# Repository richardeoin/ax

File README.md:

## AX

This repository contains hardware and software for the AX5043 and
AX5243 radios from AxSemi (now ON Semiconductor). They are probably
the same die, but the AX5243 has fewer pins.

There is [hardware](hw/) for the Raspberry Pi, C.H.I.P. and a 2mm
pitch breakout board.

The [software](sw/) has both C and Python APIs, and can be used
without the cumbersome Ax-RadioLab GUI tool. Not all features of the
radio are supported yet.

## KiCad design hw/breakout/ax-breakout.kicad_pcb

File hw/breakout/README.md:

# Hardware for ax-breakout

This folder contains the schematic files for the ax-breakout header
board.

This board breaks out a single AX5243 radio to 2mm pitch pins. *Not yet tested*

The differential match can be populated for various frequencies, using
the values found in the AX5243 datasheet. Usually this is 144MHz,
434MHz or 868MHz. `Lext` can be populated so that frequencies outside
of 400-525MHz / 800-1050MHz can be used; usually this is `22nH` for
140-154MHz.

_[Schematics](ax-breakout.sch.pdf)_

_[Board Drawings](ax-breakout.kicad_pcb.pdf)_

_[3D Rendering](ax-breakout.kicad_pcb.png)_

![Rendering of ax-breakout board](ax-breakout.kicad_pcb.png
 "Rendering of ax-breakout board")

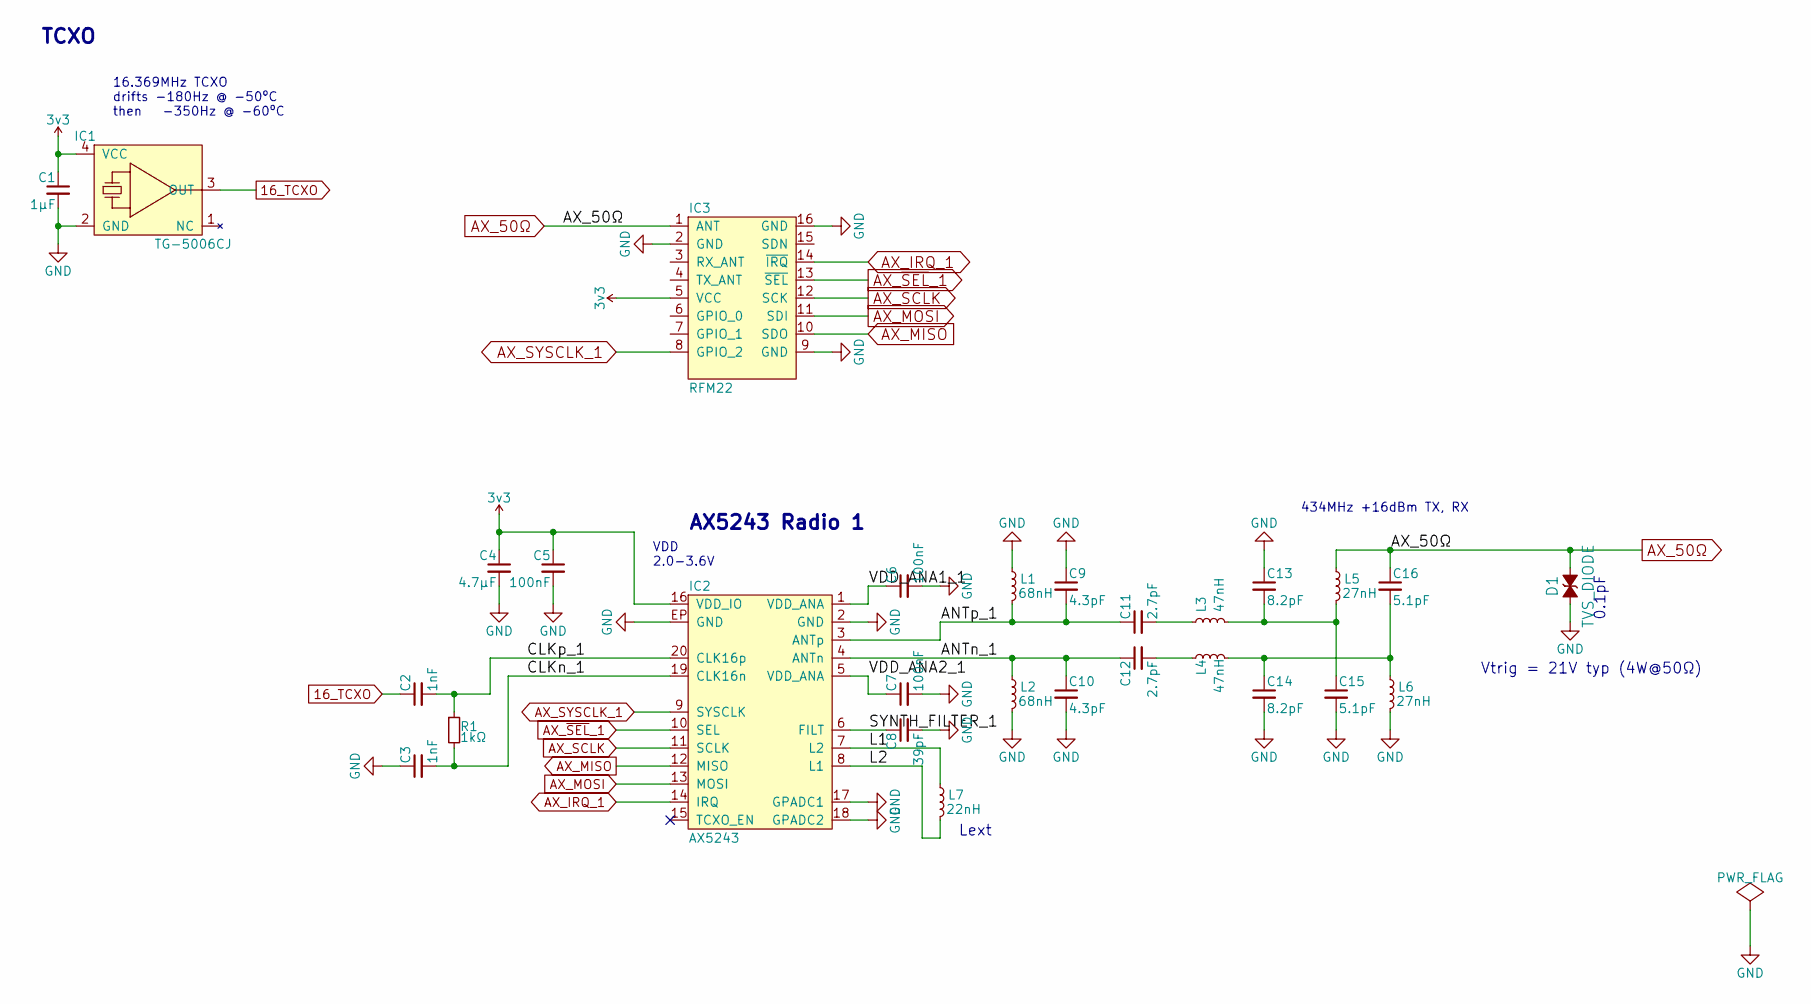
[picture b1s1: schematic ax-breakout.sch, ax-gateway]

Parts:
C1: 1µF; 0402
C2, C3: 1nF; 0402
C4: 4.7µF; 0402
C5, C6, C7: 100nF; 0402
C8: 39pF; 0402
C9, C10: 4.3pF; 0402
C11, C12: 2.7pF; 0402
C13, C14: 8.2pF; 0402
C15, C16: 5.1pF; 0402
D1: TVS_DIODE; TSLP-2-17; Farnell 2480929
IC1: TG-5006CJ; Farnell 2405790
IC2: AX5243; QFN-20-EP-AX; Farnell 2521322
IC3: RFM22; RFM22_COMPATIBLE
L1, L2: 68nH; 0402
L3, L4: 47nH; 0402
L5, L6: 27nH; 0402
L7: 22nH; 0402
R1: 1kΩ; 0402

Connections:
3v3: C1.1, C4.1, C5.1, IC1.4 (VCC), IC2.16 (VDD_IO), IC3.5 (VCC)
16_TCXO: C2.1, IC1.3 (OUT)
/ANTn_1: C10.1, C12.1, IC2.4 (ANTn), L2.1
/ANTp_1: C9.2, C11.1, IC2.3 (ANTp), L1.2
/CLKn_1: C3.2, IC2.19 (CLK16n), R1.2
/CLKp_1: C2.2, IC2.20 (CLK16p), R1.1
/L1: IC2.7 (L2), L7.1
/L2: IC2.8 (L1), L7.2
/SYNTH_FILTER_1: C8.1, IC2.6 (FILT)
/VDD_ANA1_1: C6.1, IC2.1 (VDD_ANA)
/VDD_ANA2_1: C7.1, IC2.5 (VDD_ANA)
AX_50Ω: C16.1, D1.1, IC3.1 (ANT), L5.1
AX_IRQ_1: IC2.14 (IRQ), IC3.14 (~IRQ~)
AX_MISO: IC2.12 (MISO), IC3.10 (SDO)
AX_MOSI: IC2.13 (MOSI), IC3.11 (SDI)
AX_SCLK: IC2.11 (SCLK), IC3.12 (SCK)
AX_SYSCLK_1: IC2.9 (SYSCLK), IC3.8 (GPIO_2)
AX_~SEL~_1: IC2.10 (SEL), IC3.13 (~SEL~)
GND: C1.2, C3.1, C4.2, C5.2, C6.2, C7.2, C8.2, C9.1, C10.2, C13.1, C14.2, C15.2, D1.2, IC1.2 (GND), IC2.2 (GND), IC2.17 (GPADC1), IC2.18 (GPADC2), IC2.EP (GND), IC3.2 (GND), IC3.9 (GND), IC3.16 (GND), L1.1, L2.2, L6.2
unnamed: C11.2, L3.1
unnamed: C12.2, L4.1
unnamed: C13.2, C15.1, L3.2, L5.2
unnamed: C14.1, C16.2, L4.2, L6.1

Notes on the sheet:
16.369MHz TCXO drifts -180Hz @ -50ºC then -350Hz @ -60ºC
AX5243 Radio 1
VDD 2.0-3.6V
TCXO
434MHz +16dBm TX, RX
Vtrig = 21V typ (4W@50Ω)
0.1pF
Lext

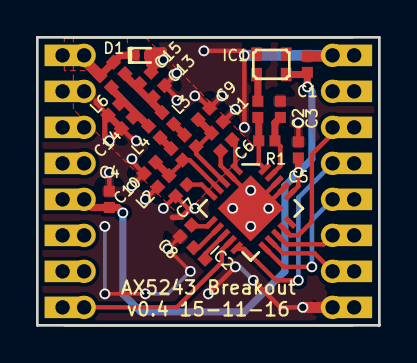
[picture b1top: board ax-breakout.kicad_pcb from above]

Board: 2 copper layers, 19.0 x 16.0 mm, 28 parts (0 on the bottom side), 23 nets.

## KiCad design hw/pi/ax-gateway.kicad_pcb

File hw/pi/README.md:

# Hardware for ax-gateway

This folder contains the schematic files for the ax-gateway header
board.

This board supports one or two AX5243 radios, with a bi-directional
antenna port for each radio. It has been tested with a
[Raspberry Pi 3 Model B](https://www.raspberrypi.org/products/raspberry-pi-3-model-b/).

The differential match can be populated for various frequencies, using
the values found in the AX5243 datasheet. Usually this is 144MHz,
434MHz or 868MHz. `Lext` can be populated so that frequencies outside
of 400-525MHz / 800-1050MHz can be used; usually this is `22nH` for
140-154MHz.

_[Schematics](ax-gateway.sch.pdf)_

_[Board Drawings](ax-gateway.kicad_pcb.pdf)_

_[3D Rendering](ax-gateway.kicad_pcb.png)_

![Assembled ax-gateway header board](ax-gateway-on-pi.jpg
 "Assembled ax-gateway header board")

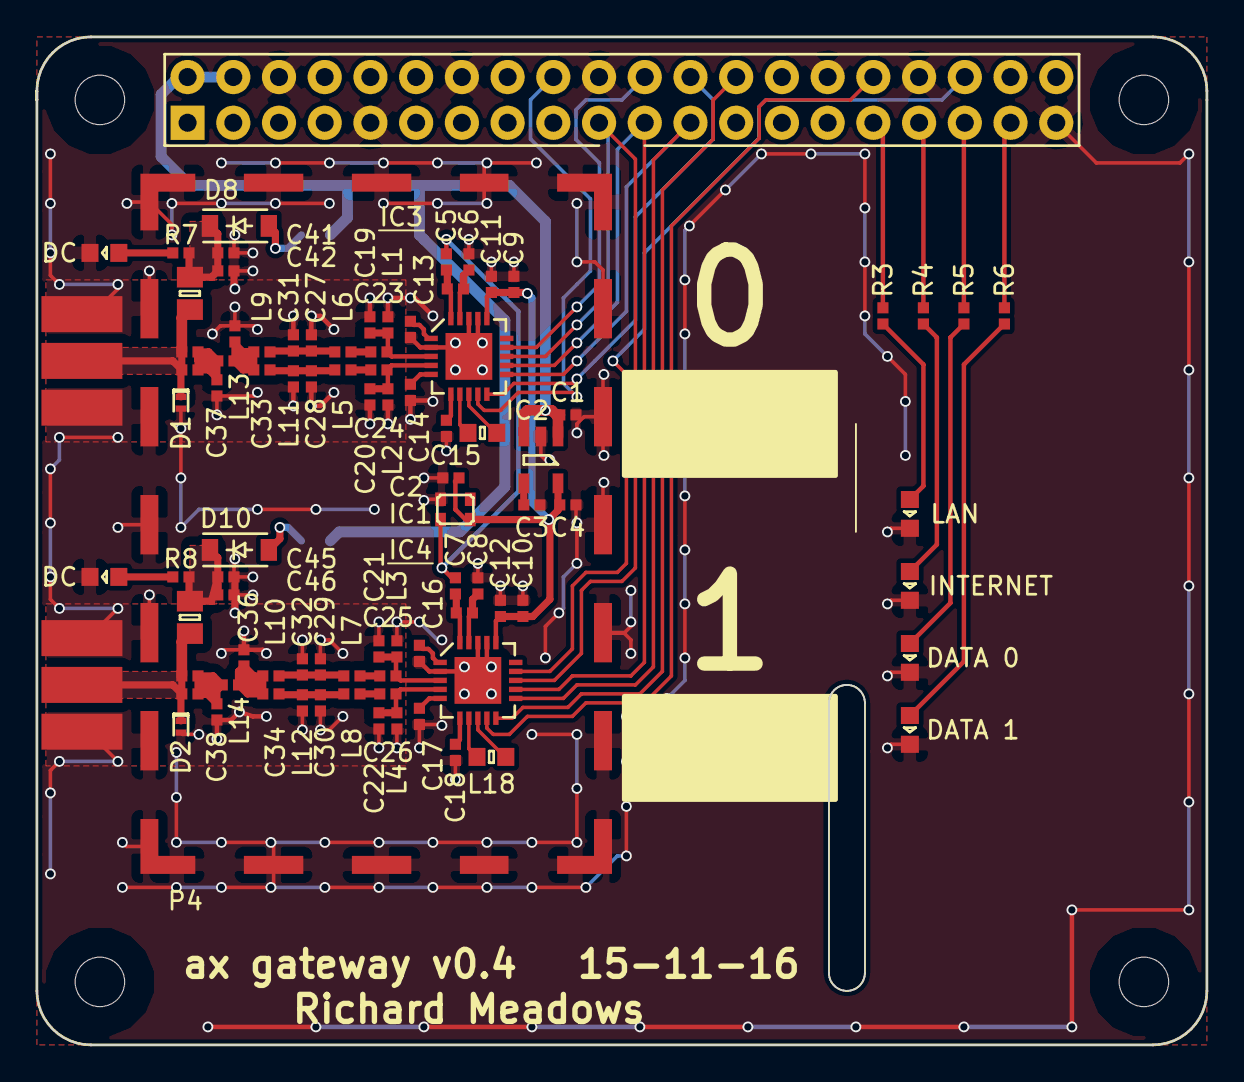
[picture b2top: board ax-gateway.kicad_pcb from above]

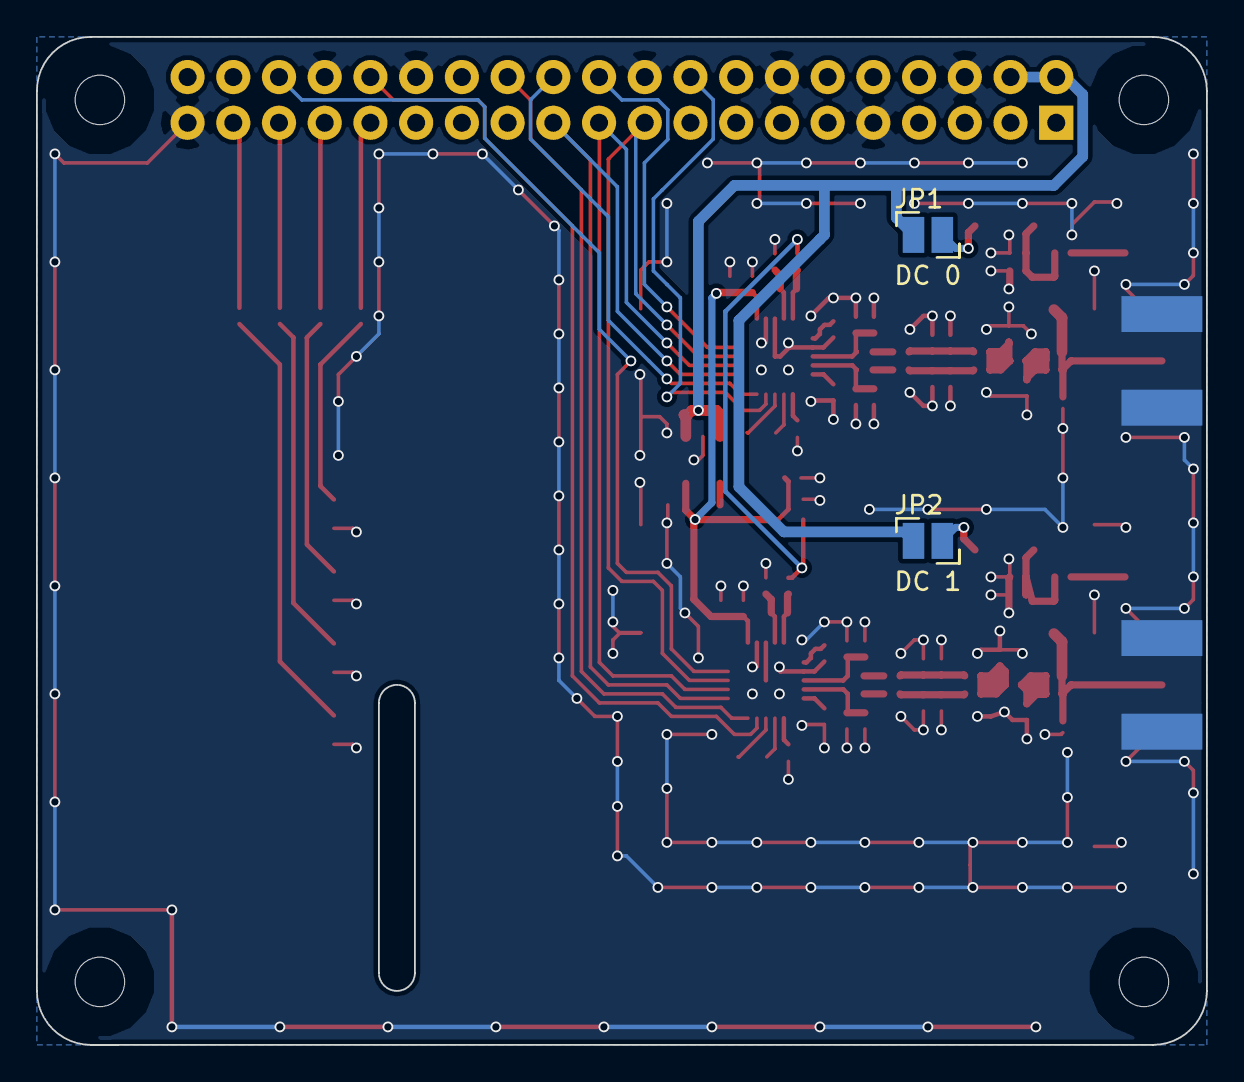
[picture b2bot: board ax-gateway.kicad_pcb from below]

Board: 2 copper layers, 65.0 x 56.0 mm, 92 parts (2 on the bottom side), 60 nets.

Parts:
C1, C2: 1µF; 0402
C3: 10nF; 0402
C4, C9, C10: 4.7µF; 0402
C5, C6, C7, C8, C39, C42, C43, C46: 1nF; 0402
C11, C12, C13, C14, C16, C17, C41, C45: 100nF; 0402
C15, C18: 39pF; 0402
C19, C20, C23, C24: 4.3pF; 0402
C21, C22: DNP; 0402
C25, C26, C32, C34: 2.7pF; 0402
C27, C28: 8.2pF; 0402
C29, C30: 3.6pF; 0402
C31, C33: 5.1pF; 0402
C35, C36, C37, C38: NOSTUFF; 0402
C40, C44: 100pF; 0402
D1, D2: TVS_DIODE; TSLP-2-17
D3: LAN; 0603-LED
D4: INTERNET; 0603-LED
D5: DATA 0; 0603-LED
D6: DATA 1; 0603-LED
D7: DC 1; 0603-LED
D8, D10: SCHOTTKY; SOD-123
D9: DC 0; 0603-LED
IC1: TG-5006CJ
IC2: TPS73433; SOT-23-5
IC3, IC4: AX5243; QFN-20-EP-AX
JP1, JP2: Jumper_NO_Small; SOLDER_JUMPER_NO
L1, L2: 68nH; 0402
L3, L4, L7, L8: 18nH; 0402
L5, L6: 47nH; 0402
L9, L11: 27nH; 0402
L10, L12: 12nH; 0402
L13, L14: 0Ω; 0402
L15, L16: 2.2µH; 0805
L17, L18: 22nH; 0603
P1: Raspberry_Pi_Conn; Rasberry_Pi_3
P2, P3: COAX; SMA-EDGE
P4: PAD; BMI-S-x05
R1, R2: 1kΩ; 0402
R3, R4, R5, R6, R7, R8: 330Ω; 0402

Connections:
3v3: C2.1, C4.1, C9.1, C10.1, C11.1, C12.1, IC1.4, IC2.5, IC3.16, IC4.16
16_TCXO: C5.1, C7.1, IC1.3
/ANTn_0: C20.1, C24.1, IC3.4, L2.1
/ANTn_1: C22.1, C26.1, IC4.4, L4.1
/ANTp_0: C19.2, C23.1, IC3.3, L1.2
/ANTp_1: C21.2, C25.1, IC4.3, L3.2
/AX_50Ω_0: C33.1, C35.1, L9.1, L13.1
/AX_50Ω_1: C34.1, C36.1, L10.1, L14.1
/AX_ANT_0: C39.2, C40.2, D1.1, L15.2, P2.1
/AX_ANT_1: C43.2, C44.2, D2.1, L16.2, P3.1
/AX_F_0: C37.1, C39.1, C40.1, L13.2
/AX_F_1: C38.1, C43.1, C44.1, L14.2
/CLKn_0: C6.2, IC3.19, R1.2
/CLKn_1: C8.2, IC4.19, R2.2
/CLKp_0: C5.2, IC3.20, R1.1
/CLKp_1: C7.2, IC4.20, R2.1
/DC_0: C41.1, C42.1, D8.1, L15.1, R7.1
/DC_1: C45.1, C46.1, D10.1, L16.1, R8.1
/L1_0: IC3.7, L17.1
/L1_1: IC4.7, L18.1
/L2_0: IC3.8, L17.2
/L2_1: IC4.8, L18.2
/SYNTH_FILTER_0: C15.1, IC3.6
/SYNTH_FILTER_1: C18.1, IC4.6
/VDD_ANA1_0: C13.1, IC3.1
/VDD_ANA1_1: C16.1, IC4.1
/VDD_ANA2_0: C14.1, IC3.5
/VDD_ANA2_1: C17.1, IC4.5
AX_IRQ_0: IC3.14, P1.22
AX_IRQ_1: IC4.14, P1.36
AX_MISO: IC3.12, IC4.12, P1.21
AX_MOSI: IC3.13, IC4.13, P1.19
AX_SCLK: IC3.11, IC4.11, P1.23
AX_SYSCLK_0: IC3.9, P1.18
AX_SYSCLK_1: IC4.9, P1.32
AX_~SEL~_0: IC3.10, P1.24
AX_~SEL~_1: IC4.10, P1.26
DATA_LED_0: P1.35, R5.1
DATA_LED_1: P1.37, R6.1
GND: C1.2, C2.2, C3.2, C4.2, C6.1, C8.1, C9.2, C10.2, C11.2, C12.2, C13.2, C14.2, C15.2, C16.2, C17.2, C18.2, C19.1, C20.2, C21.1, C22.2, C27.1, C28.2, C29.1, C30.2, C31.2, C32.2, C35.2, C36.2, C37.2, C38.2, C41.2, C42.2, C45.2, C46.2, D1.2, D2.2, D3.1, D4.1, D5.1, D6.1, D7.1, D9.1, IC1.2, IC2.2, IC3.2, IC3.17, IC3.18, IC3.EP, IC4.2, IC4.17, IC4.18, IC4.EP, L1.1, L2.2, L3.1, L4.2, L11.2, L12.2, P1.6, P1.9, P1.14, P1.20, P1.25, P1.30, P1.34, P1.39, P2.2, P3.2, P4.1
INTERNET_LED: P1.33, R4.1
LAN_LED: P1.31, R3.1
unnamed: C3.1, IC2.4
unnamed: C23.2, L5.1
unnamed: C24.2, L6.1
unnamed: C25.2, L7.1
unnamed: C26.2, L8.1
unnamed: C27.2, C31.1, L5.2, L9.2
unnamed: C28.1, C33.2, L6.2, L11.1
unnamed: C29.2, C32.1, L7.2, L10.2
unnamed: C30.1, C34.2, L8.2, L12.1
unnamed: D3.2, R3.2
unnamed: D4.2, R4.2
unnamed: D5.2, R5.2
unnamed: D6.2, R6.2
unnamed: D7.2, R8.2
unnamed: D8.2, JP1.2
unnamed: D9.2, R7.2
unnamed: D10.2, JP2.2
VDD: C1.1, IC2.1, IC2.3, JP1.1, JP2.1, P1.2, P1.4

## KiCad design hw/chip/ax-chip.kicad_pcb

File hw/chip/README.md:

# Hardware for ax-chip

This folder contains the schematic files for the ax-chip header
board.

The board uses a single AX5043 radio, with separate antenna ports for
transmit and receive. The recieve port has an integrated Low Noise
Amplifier (LNA). *Not yet tested*

The LNA used is an
[Avago MGA-62563](http://www.avagotech.com/docs/AV02-1237EN), but a
MGA-61563 or MGA-68563 could also be used, by adjusting the bias
resistor R12. By default the MGA-62563 is biased to 3.3V, 30mA.

| Frequency (MHz) | Theoretical NF @ 25ºC |
|---|---
| 144 | 1.3
| 434 | 0.9

The differential match following the LNA is tuned to for both 144MHz
and 434MHz (blue line in this [plot](144_434_S21.png)). The single
ended match on the transmit port is tuned for 144MHz, although other
values can be found in the AX5043 datasheet.

`Lext` can be populated so that frequencies outside of 400-525MHz /
800-1050MHz can be used; usually this is `22nH` for 140-154MHz.

_[Schematics](ax-chip.sch.pdf)_

_[Board Drawings](ax-chip.kicad_pcb.pdf)_

_[3D Rendering](ax-chip.kicad_pcb.png)_

<!-- ![Assembled ax-gateway header board](ax-gateway-on-pi.jpg -->
<!--  "Assembled ax-gateway header board") -->

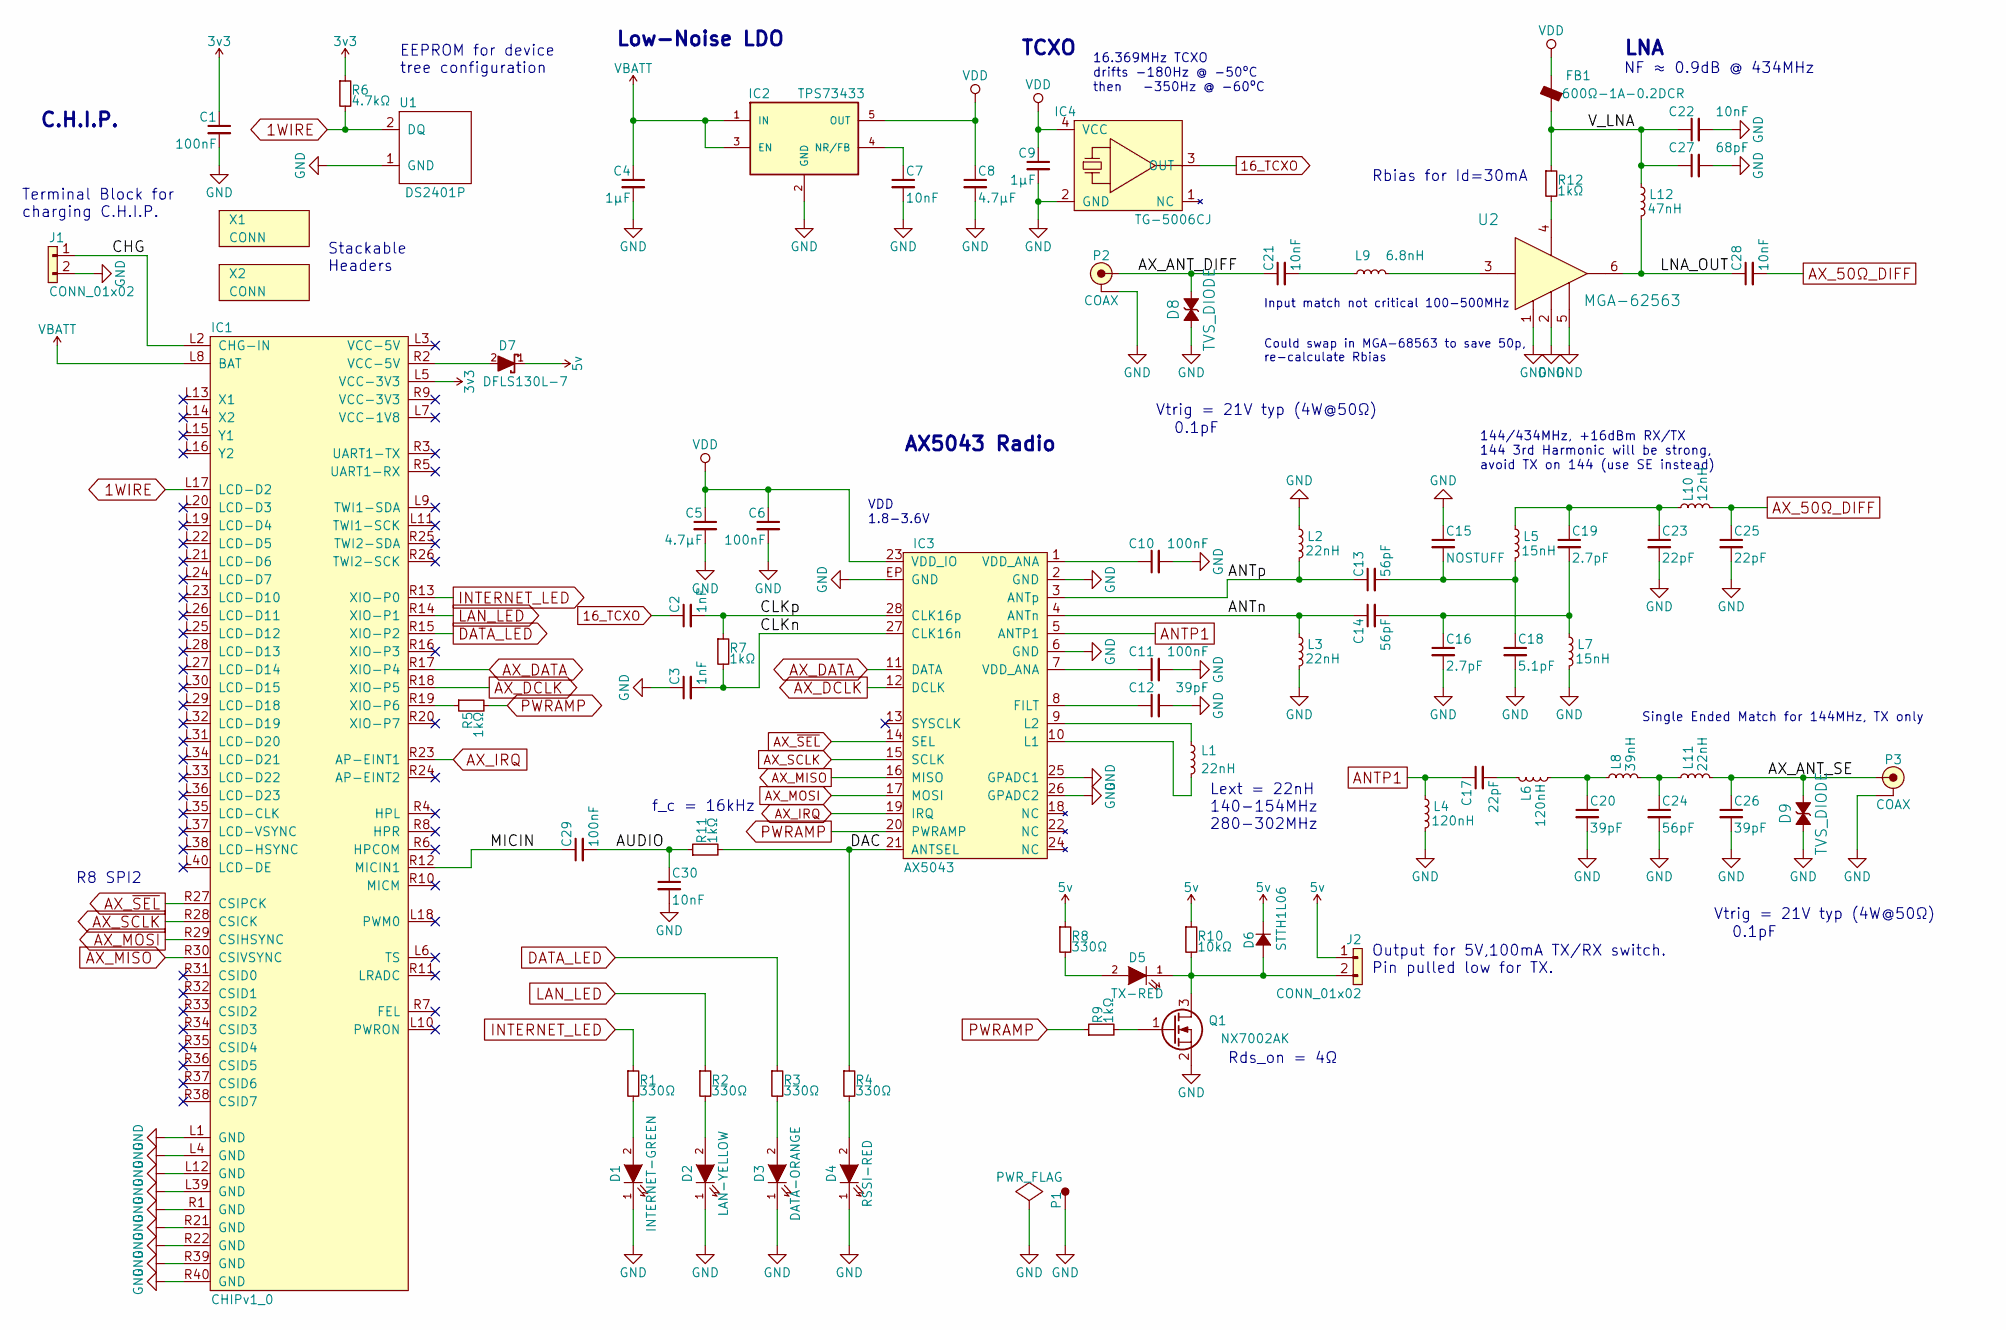
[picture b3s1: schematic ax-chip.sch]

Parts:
C1, C6, C10, C11, C29: 100nF; 0402
C2, C3: 1nF; 0402
C4, C9: 1µF; 0402
C5, C8: 4.7µF; 0402
C7, C22, C30: 10nF; 0402
C12, C20, C26: 39pF; 0402
C13, C14, C24: 56pF; 0402
C15: NOSTUFF; 0402
C16, C19: 2.7pF; 0402
C17, C23, C25: 22pF; 0402
C18: 5.1pF; 0402
C21, C28: 10nF; 0402; Farnell 8819734
C27: 68pF; 0402
D1: INTERNET-GREEN; 1206_LED_REVERSE; Farnell 2217901
D2: LAN-YELLOW; 1206_LED_REVERSE; Farnell 2217902
D3: DATA-ORANGE; 1206_LED_REVERSE; Farnell 2099254
D4: RSSI-RED; 1206_LED_REVERSE; Farnell 2217903
D5: TX-RED; 1206_LED_REVERSE; Farnell 2217903
D6: STTH1L06; DO-214AC-SMA; Farnell 8165505
D7: DFLS130L-7; SOD-123; Farnell 1843673
D8, D9: TVS_DIODE; TSLP-2-17; Farnell 2480929
FB1: 600Ω-1A-0.2DCR; 0603; Farnell 1635706
IC1: CHIPv1_0
IC2: TPS73433; SOT-23-5; Farnell 2382987
IC3: AX5043; QFN-28-EP-AX; Farnell 2521320
IC4: TG-5006CJ; Farnell 2405790
J1, J2: CONN_01x02; TerminalBlock_Pheonix_PT-3.5mm_2pol
L1, L2, L3: 22nH; 0603
L4, L6: 120nH; 0603
L5: 15nH; 0402; Farnell 1762621
L7: 15nH; 0402
L8: 39nH; 0402
L9: 6.8nH; 0402; Farnell 1762612
L10: 12nH; 0603; Digikey 490-6862-1-ND
L11: 22nH; 0402
L12: 47nH; 0402; Farnell 1343090
P1: PAD; BMI-S-x05; Farnell 2497723
P2, P3: COAX; SMA-EDGE; Farnell 1608592
Q1: NX7002AK; SOT-23; Farnell 2191746
R1, R2, R3, R4, R8: 330Ω; 0402
R5, R7, R9, R11, R12: 1kΩ; 0402
R6: 4.7kΩ; 0402
R10: 10kΩ; 0402
U1: DS2401P; TSOT-6-MK06A; Farnell 2519009
U2: MGA-62563; SC-70-6; Farnell 7820453
X1, X2: CONN

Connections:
1WIRE: IC1.L17 (LCD-D2), R6.2, U1.2 (DQ)
3v3: C1.1, IC1.L5 (VCC-3V3), R6.1
5v: D6.1 (K), D7.1 (K), J2.1, R8.1, R10.1
16_TCXO: C2.1, IC4.3 (OUT)
/ANTn: C14.1, IC3.4 (ANTn), L3.1
/ANTp: C13.1, IC3.3 (ANTp), L2.2
/AUDIO: C29.2, C30.1, R11.1
/AX_ANT_DIFF: C21.1, D8.1, P2.1 (RF)
/AX_ANT_SE: C26.1, D9.1, L11.2, P3.1 (RF)
/CHG: IC1.L2 (CHG-IN), J1.1
/CLKn: C3.2, IC3.27 (CLK16n), R7.2
/CLKp: C2.2, IC3.28 (CLK16p), R7.1
/DAC: IC3.21 (ANTSEL), R4.1, R11.2
/LNA_OUT: C28.1, L12.2, U2.6
/MICIN: C29.1, IC1.R12 (MICIN1)
/V_LNA: C22.1, C27.1, FB1.2, L12.1, R12.1
ANTP1: C17.1, IC3.5 (ANTP1), L4.1
AX_50Ω_DIFF: C25.1, C28.2, L10.2
AX_DATA: IC1.R17 (XIO-P4), IC3.11 (DATA)
AX_DCLK: IC1.R18 (XIO-P5), IC3.12 (DCLK)
AX_IRQ: IC1.R23 (AP-EINT1), IC3.19 (IRQ)
AX_MISO: IC1.R30 (CSIVSYNC), IC3.16 (MISO)
AX_MOSI: IC1.R29 (CSIHSYNC), IC3.17 (MOSI)
AX_SCLK: IC1.R28 (CSICK), IC3.15 (SCLK)
AX_~SEL~: IC1.R27 (CSIPCK), IC3.14 (SEL)
DATA_LED: IC1.R15 (XIO-P2), R3.1
GND: C1.2, C3.1, C4.2, C5.2, C6.2, C7.2, C8.2, C9.2, C10.2, C11.2, C12.2, C15.1, C16.2, C18.2, C20.2, C22.2, C23.2, C24.2, C25.2, C26.2, C27.2, C30.2, D1.1 (K), D2.1 (K), D3.1 (K), D4.1 (K), D8.2, D9.2, IC1.L1 (GND), IC1.L4 (GND), IC1.L12 (GND), IC1.L39 (GND), IC1.R1 (GND), IC1.R21 (GND), IC1.R22 (GND), IC1.R39 (GND), IC1.R40 (GND), IC2.2 (GND), IC3.2 (GND), IC3.6 (GND), IC3.25 (GPADC1), IC3.26 (GPADC2), IC3.EP (GND), IC4.2 (GND), J1.2, L2.1, L3.2, L4.2, L7.2, P1.1, P2.2 (GND), P3.2 (GND), Q1.2 (S), U1.1 (GND), U2.1, U2.2, U2.5
INTERNET_LED: IC1.R13 (XIO-P0), R1.1
LAN_LED: IC1.R14 (XIO-P1), R2.1
unnamed: C7.1, IC2.4 (NR/FB)
unnamed: C10.1, IC3.1 (VDD_ANA)
unnamed: C11.1, IC3.7 (VDD_ANA)
unnamed: C12.1, IC3.8 (FILT)
unnamed: C13.2, C15.2, C18.1, L5.2
unnamed: C14.2, C16.1, C19.2, L7.1
unnamed: C17.2, L6.1
unnamed: C19.1, C23.1, L5.1, L10.1
unnamed: C20.1, L6.2, L8.1
unnamed: C21.2, L9.1
unnamed: C24.1, L8.2, L11.1
unnamed: D1.2 (A), R1.2
unnamed: D2.2 (A), R2.2
unnamed: D3.2 (A), R3.2
unnamed: D4.2 (A), R4.2
unnamed: D5.1 (K), D6.2 (A), J2.2, Q1.3 (D), R10.2
unnamed: D5.2 (A), R8.2
unnamed: D7.2 (A), IC1.R2 (VCC-5V)
unnamed: IC1.R19 (XIO-P6), R5.1
unnamed: IC3.9 (L2), L1.1
unnamed: IC3.10 (L1), L1.2
unnamed: L9.2, U2.3
unnamed: Q1.1 (G), R9.2
unnamed: R12.2, U2.4
PWRAMP: IC3.20 (PWRAMP), R5.2, R9.1
VBATT: C4.1, IC1.L8 (BAT), IC2.1 (IN), IC2.3 (EN)
VDD: C5.1, C6.1, C8.1, C9.1, FB1.1, IC2.5 (OUT), IC3.23 (VDD_IO), IC4.4 (VCC)

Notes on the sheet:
16.369MHz TCXO drifts -180Hz @ -50ºC then -350Hz @ -60ºC
AX5043 Radio
VDD 1.8-3.6V
144/434MHz, +16dBm RX/TX 144 3rd Harmonic will be strong, avoid TX on 144 (use SE instead)
C.H.I.P.
TCXO
Low-Noise LDO
Lext = 22nH 140-154MHz 280-302MHz
R8 SPI2
EEPROM for device tree configuration
Single Ended Match for 144MHz, TX only
NF ≈ 0.9dB @ 434MHz
Stackable Headers
Terminal Block for charging C.H.I.P.
Output for 5V,100mA TX/RX switch. Pin pulled low for TX.
Rds_on = 4Ω
f_c = 16kHz
LNA
Rbias for Id=30mA
Could swap in MGA-68563 to save 50p, re-calculate Rbias
Input match not critical 100-500MHz
Vtrig = 21V typ (4W@50Ω)
0.1pF

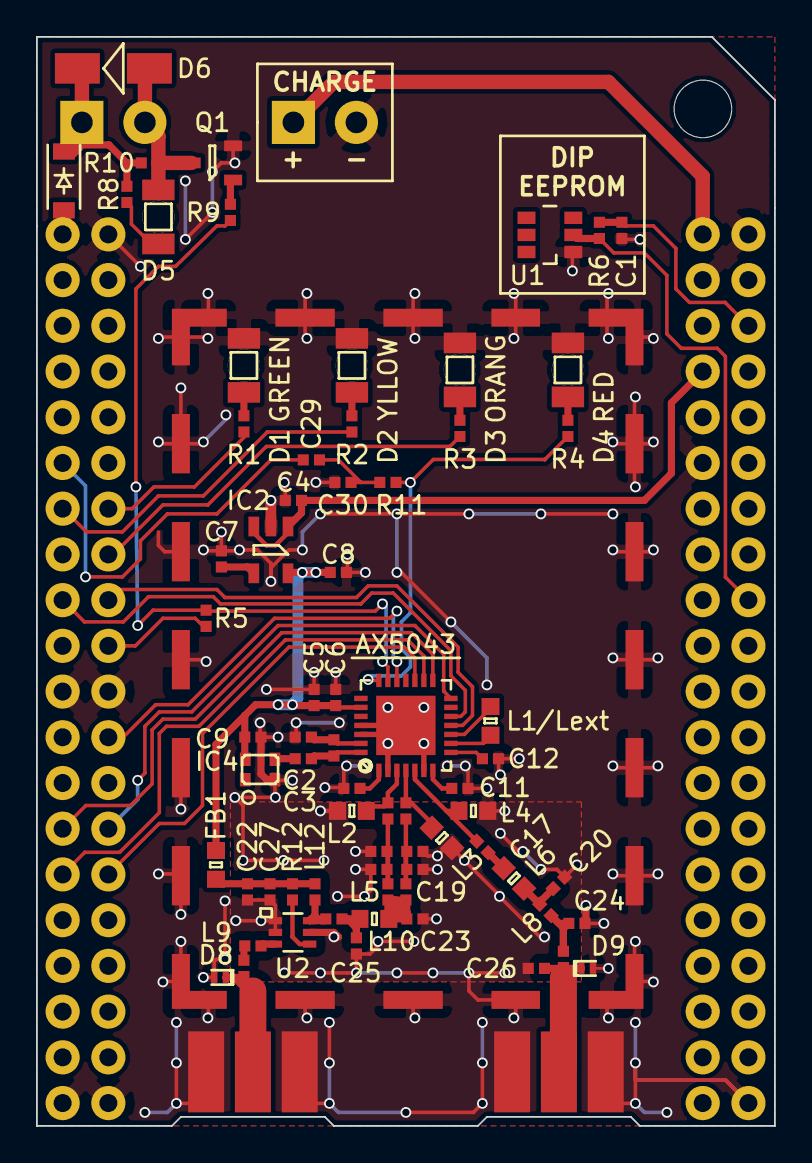
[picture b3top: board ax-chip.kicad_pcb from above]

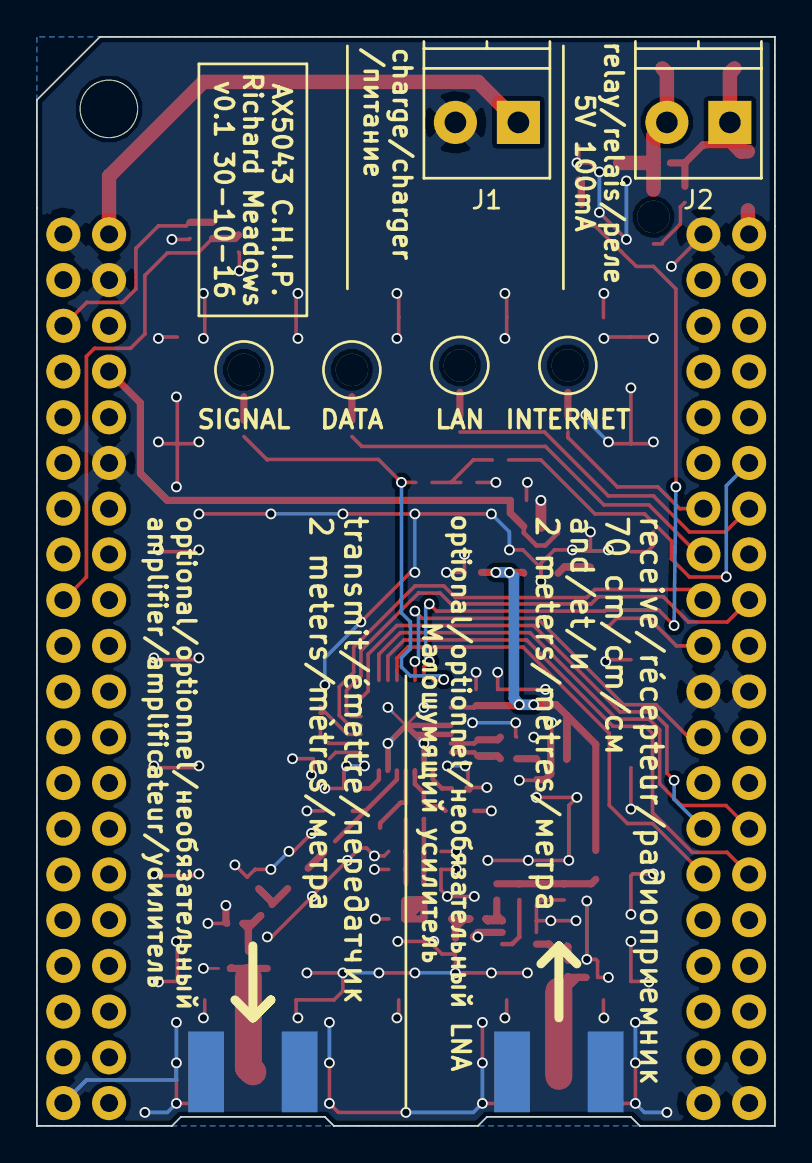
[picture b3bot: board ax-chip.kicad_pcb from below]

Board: 2 copper layers, 41.0 x 60.5 mm, 76 parts (3 on the bottom side), 56 nets.

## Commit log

2016-08-10 [gateway] initial hardware v0.1
2016-08-10 add gitignore
2016-08-12 [gateway] fix farnell code for shield
2016-08-28 [pi] added initial code for raspberry pi
2016-08-28 [hw] add images
2016-08-28 [hw] add readme and rendering
2016-08-28 [pi] added prog manual reference
2016-08-28 [hw] resize hw images
2016-09-30 [pi] initial transmit demo
2016-09-30 [pi] update file description in README
2016-10-01 [pi] add calculations for tx variables, fix FIFO operation
2016-10-01 [hw] spelling
2016-10-02 [pi] add more rx parameters
2016-10-02 [pi] add example modes
2016-10-02 [pi] fix modulation values, add shorter encoding values
2016-10-02 [pi] refactoring for API as described in README.md
2016-10-07 [hw] add l_ext
2016-10-07 [hw] add silk fields for noting frequency
2016-10-15 [pi] control vco type
2016-10-19 [pi] don't write preamble to fifo in ax_fifo_tx_data
2016-10-19 [ax,tx] set modulation, encoding correctly, wait for fifo space on transmit
2016-10-19 [ax] fix status word for fifo_write
2016-10-19 [ax,rx] rx working
2016-10-19 [ax] tidy up, re-arrange hw_init
2016-10-19 [ax] callbacks to enable/disable tcxo
2016-10-19 [ax] callback for spi transfer, wiring pi now just in ax_test.c
2016-10-19 [ax] skip first byte
2016-10-19 [ax] put ax library into a subfolder
2016-10-19 [pi] bump SPI speed
2016-10-20 [ax] print rssi on receive
2016-10-20 [ax] nrzi works with no FEC
2016-10-20 [ax] enable carrier frequency tracking, output rf offset
2016-10-20 [ax] add note about odd AFC behaviour with bit stuffing
2016-10-21 [ax] calculate more rx parameters
    IF frequency, decimation, fsk deviation
2016-10-21 [ax] calculate some values in the rx parameters sets
    test out on RX parameter set 3
2016-10-21 [ax] bugfix, set agc decay
2016-10-21 [ax] header for calculations
2016-10-22 [ax] finished rx parameter sets
2016-10-22 [ax] bugfix, use correct width forfreq value
2016-10-22 [ax] bugfix; AGC gain was not being frozen correctly
2016-10-22 [ax] bugfix; fskdev - actually use value, change k_sf to 0.8
2016-10-22 [ax] switch over the calculated rx parameter values
2016-10-23 [ax] add option for continuous receiving settings, tidy up
2016-10-23 [ax] packet controller parameters
2016-10-23 [ax] update note about f_pllrng
2016-10-24 [python] initial implementation of python interface
2016-10-24 [ax] tidy up unused code
2016-10-24 [ax] fix callback declaration
2016-10-24 [ax] patch c->python rx callback
2016-10-24 [ax] add ax_off function to header
2016-10-24 [ax] add error code for vco ranging failure
2016-10-25 [python] access values from ax_reg_values.h from python
2016-10-25 [ax] call rx callback
2016-10-25 [python] select vco type based on frequency, use enums
2016-10-25 [python] demo callback function
2016-10-26 [ax,python] implement a polling-based interface for receive.
    This makes sense for both C and Python interfaces, while being easier
    to understand and less platform dependant.
    C: microcontroller gets hardware interrupt to wake from sleep, and
    then calls polling function.
    Python: call polling function every x milliseconds. This is a minor
    overhead compared to running python. The alternative is to use a
2016-10-26 [ax] use afsk parameters when transmitting afsk
2016-10-26 [ax] parameters for receving afsk
2016-10-26 [ax] update aprs modulation
2016-10-26 [ax] afsk test working
2016-10-27 [ax] got raw packet match mode working
    breifly broken python interface
2016-10-27 [ax] adjust sync match threashold
2016-10-29 [ax] set modulation factor m once, user sets shaping mode
2016-10-29 [ax] rename mode examples
2016-10-29 [ax] initially got FEC working
2016-10-29 [ax] fec; set preamble detect, ensure framing and encoding are good
2016-10-29 [ax] update tests
2016-10-29 [ax] continous FEC
2016-10-29 [ax] add to afsk settings, afsk receive not working
2016-10-30 [ax] refactor tweakable parameter calcuations into ax_params.{c,h}
2016-10-30 [ax] continue refactor
2016-10-30 [ax] set max_delta_carrier to 1kHz by default
2016-10-30 [ax] update README, notes about waking from DEEPSLEEP
2016-10-30 [ax] refactor names, tidy up
2016-10-30 [ax] expose tweakable parameters as a separate initialisation step
2016-10-30 [python] update python for latest API changes
2016-10-30 [ax] implement ax_adjust_frequency
2016-10-30 [chip] added chip hardware
2016-10-31 [ax] set modulation index m correctly for AFSK.
    AFSK demodulation still not functional however.
2016-10-31 [ax] mask modulation values correctly
2016-11-07 [ax] support long packets, tested to 255 bytes
2016-11-07 [ax] for long packets, write smallest section of packet first
    for 255 bytes packets this should reduce the time spent waiting for the fifo to empty
    however this could be improved further by using a FIFO threashold interrupt
2016-11-16 [chip hw] add LNA, remove dc power inject
2016-11-20 [ax] fix test for inversion+fec
2016-11-20 [ax] configure lposc and wakeup timer
2016-11-20 [ax] improve debug messages
2016-11-20 [ax] allow all "freqgain" parameters to be set independantly
2016-11-21 [ax] add debugging for tracking registers
2016-11-22 [ax wor] initial support for wake-on-radio, not yet tested
2016-11-22 [pi hw] add l_ext
2016-11-22 [chip hw] update chip sch part
2016-11-22 add to gitignore
2016-11-22 re-orgainse folder structure
2016-11-22 add overall README
2016-11-22 update gitignore
2016-11-22 [breakout hw] add breakout board
2016-11-22 [hw] add readme for hardware
2016-11-22 [hw] fix README
2016-11-22 [hw] update readme, add artifacts
2016-11-22 [hw] tidy boms, regen artifacts, update READMEs
2016-11-22 [hw] update READMEs
2016-11-22 [hw[ put plot in correct folder
2016-11-22 [hw] add image of breakout to main readme
2016-11-22 [chip hw] clairify wording
2016-11-22 [ax] add to README
2016-11-25 [python] update modulation types, refactor a bit
2016-11-25 [python add AxRadioGMSK
2016-11-26 [python] frequencies in MHz
2016-11-26 [python] started installation instructions
2016-11-26 [habitat] started habitat uploader
2016-11-26 [python] update installation instructions
2016-11-26 [ax] remove unnessesary build dep
2016-11-26 [gateway] fix stupid
2016-11-26 [python] ffi.string for python2 compatibility
2016-11-26 [gatewway] use UploadThread, logging to file
2016-11-26 [python] load gateway parameters from gateway.yaml
2016-11-26 [python] successfully test transmit
2016-11-27 [chip hw] fix board drawings filename
2016-11-27 [ax] add fsk mode for testing, this works fine
2016-11-30 [sw README] add examples.md
2016-12-01 [sw gatway] add note about editing gateway yaml
2016-12-08 [ax] use VCO type in PLLVCODIV reg correctly
2016-12-08 [ax_test] use SPI_CHANNEL macro
2016-12-08 [python] turn off FEC by default
2016-12-08 [ax] spelling
2016-12-13 [python] use normal fsk mode by default
2016-12-13 [gateway] hard-code test frequency
2016-12-27 [dummy] add dummy python build, so that python can be run without hardware
2016-12-27 [python] add debug option to build scripts, off by default
2016-12-27 [ax] tidy compiler warn
2017-01-15 [ax] fix include paths
2017-01-21 [ax] add c functions for pin functions, and switching between diff and single ended ports
2017-01-21 [ax] add tx_1k_zeros
2017-01-21 [ax,python] add cw modulation option to python
2017-01-21 [ax,python] add support for setting power fraction
2017-01-21 [ax] add support for fast frequency switches during a transmission
2017-01-21 [ax,python] AxRadioAPRS supports configurable deviation
2017-01-22 [gmsk-gateway] add argparse, offine option
2017-01-22 [gmsk-gateway] print notice of errors, don't crash
2017-01-22 [ax,python] add flag for continous rx, on by default
2017-01-22 [ax,python] use raw packet match when not using fec mode
2017-01-22 [ax,python] add metadata to receive callback
2017-01-23 [ax,python] ax_off only waits for tx operations. Track radio state in py
2017-01-23 [ax,python] receive timeout
2017-01-23 [ax] clear fifo before starting tx operations
2017-01-23 [ax] add metadata to rx_pkt if metadata is requested in pkt_store_flags
2017-01-26 [ax] discard packets that are too long for ax_packet structure
2017-02-01 [ax] don't use define in header file, cffi no like
2017-02-01 [gmsk-gateway] improve information printing, error handling
2017-02-02 [v0.2] add changelog for version 0.2
2017-02-03 [ubseds22] hard-code frequency for ubseds22
2017-02-04 [python aprs] fix aprs framing
2017-02-04 [gmsk-gateway] don't display 'uploading remaining packets...' message when offline
2017-02-04 [autogen] add example of autogenerating c structures using python
2017-02-04 [leds] add rx and habitat LEDs. pip install wiringpi2 and specify -l to enable
2017-02-07 [ax] config includes power limit
2017-02-09 [python] use ffi.unpack instead of ffi.string as this isn't affected by zero bytes
2017-02-09 [ax,python] set pkt_accept_flags through config, used to possibly ignore crc failures
2017-02-09 [gateway] add reed-solomon
2017-02-10 [ax] bugfix: prevent hang on slow callback response
    if the rx callback takes a long time to return, the FIFO may
    completely fill such that the register FIFOCOUNT = 256 when
    ax_fifo_rx_data is eventually called again. This value was locally
    stored in a uint8_t, and thus the value 256 was stored as 0. Therefore
    ax_fifo_rx_data made no further attempts to read the FIFO, and no data
    was received until the radio was reset. Fix with correct local storage
2017-02-12 [chip] initial sw for chip
2017-02-25 [ax] dac config
2017-03-03 [python,bugfix] set default modulation index correctly for fsk modes
2017-03-05 [ax] add more debugging strings
2017-03-05 [dac] shift dac values down, this is a sensible default
2017-03-05 [ax,afsk] set afsk parameters separately for transmit and receive
    AFSKSPACE/AFSKMARK/AFSKSHIFT
2017-03-20 [ax_hw] implement full ax_hw_write_register_32 for faster 32 bit writes
2017-03-21 [ax_params] name drg_corr_frac correctly
2017-03-24 [ax_params] reduce drg_corr_frac: faster bit lock but more jitter
2017-03-31 [ax] fix ranging error when only one VCO is used
2017-04-02 [dummy] write header
2017-04-02 [chip] add digikey, farnell order codes
2017-04-17 [readme] update install instructions
2017-04-17 [python,gmsk] cont option
2017-04-17 [chip] `singleport` build option for CHIP, used with non-standard hardware
2017-04-17 [chip,installing] update
2017-04-26 [readme] added folder changes to install instructions
2017-04-29 [gmsk] use mode x: 12k bitrate, gaussian filter
2017-04-29 [autotune] add autotune functionality
2017-05-01 [gateway] add support for ssdv, re-write noise packets, autotune
2017-05-05 [readme] add updating instructions
2017-05-05 [readme] add heading
2017-05-05 [readme] added dependancy, note about dependancies when updating
2017-05-07 [ssdv] bugfix in offline mode
2017-05-13 [chip] update installation instructions
2017-07-01 [readme] spelling
2019-04-06 [ax] fix define error - Issue #3 reported by @callpla
    Thanks!
    Closes #3
